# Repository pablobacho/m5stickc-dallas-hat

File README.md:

# m5stickc-dallas-hat
Adapter for DS18B20 temperature sensor and M5StickC

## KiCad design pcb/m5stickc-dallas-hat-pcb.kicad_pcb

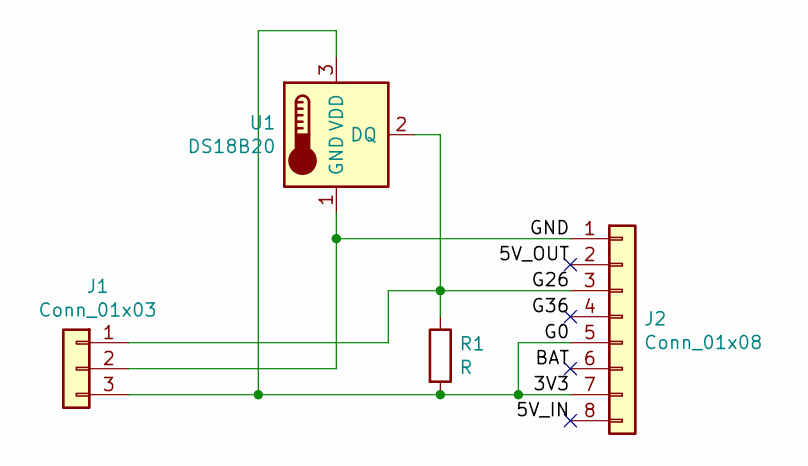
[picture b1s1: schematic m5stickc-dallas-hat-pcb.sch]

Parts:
J1: Conn_01x03; PinHeader_1x03_P2.54mm_Vertical
J2: Conn_01x08; PinHeader_1x08_P2.54mm_Horizontal
R1: R; R_Axial_DIN0207_L6.3mm_D2.5mm_P7.62mm_Horizontal
U1: DS18B20; TO-92_Inline

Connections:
/3V3: J1.3, J2.5, J2.7, R1.2, U1.3 (VDD)
/5V_IN: J2.8
/5V_OUT: J2.2
/BAT: J2.6
/G26: J1.1, J2.3, R1.1, U1.2 (DQ)
/G36: J2.4
/GND: J1.2, J2.1, U1.1 (GND)

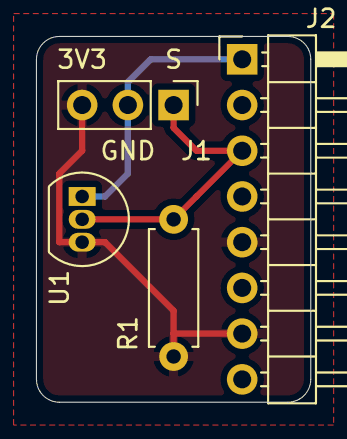
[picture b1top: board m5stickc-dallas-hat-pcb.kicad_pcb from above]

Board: 2 copper layers, 15.2 x 20.3 mm, 4 parts (0 on the bottom side), 3 nets.

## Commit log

2019-09-25 First prototype
2019-09-29 production files
